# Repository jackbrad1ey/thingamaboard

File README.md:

# Thingamaboard

A custom keyboard designed and manufactured for myself. Programmed using STM32CubeIDE and Jetbrains Fleet, designed using [Ergogen](https://github.com/ergogen/ergogen), AutoCAD and Solidworks. This board was developed with portability and ergonomics in mind. It adopts a columnar, alice-like layout with three-key thumb clusters, allowing for ergonomic typing in a relatively small and portable form factor.

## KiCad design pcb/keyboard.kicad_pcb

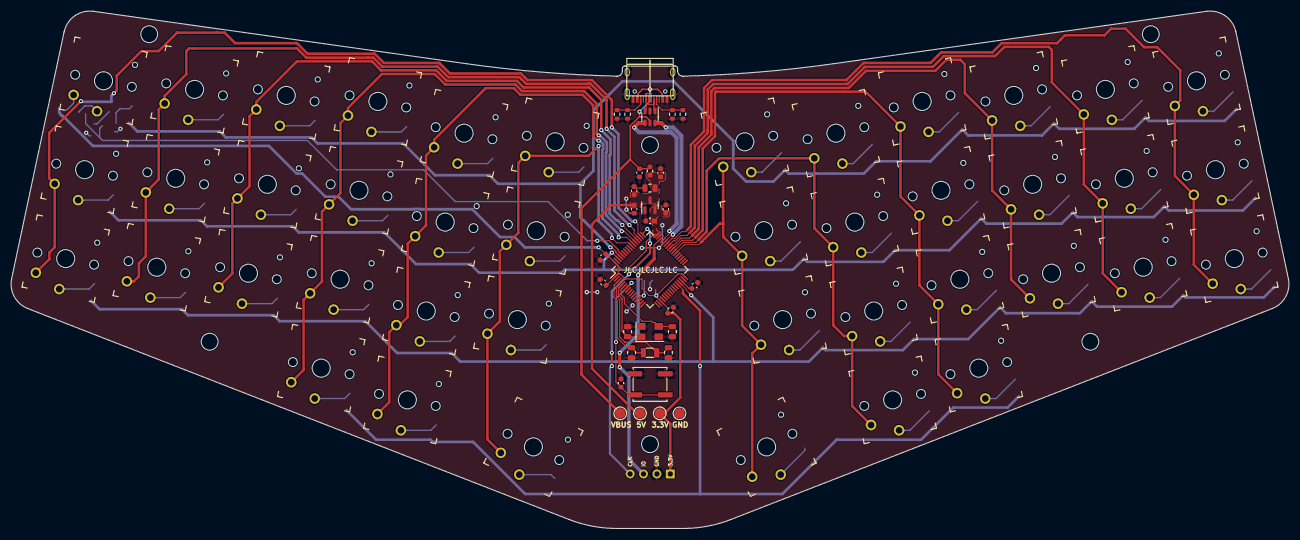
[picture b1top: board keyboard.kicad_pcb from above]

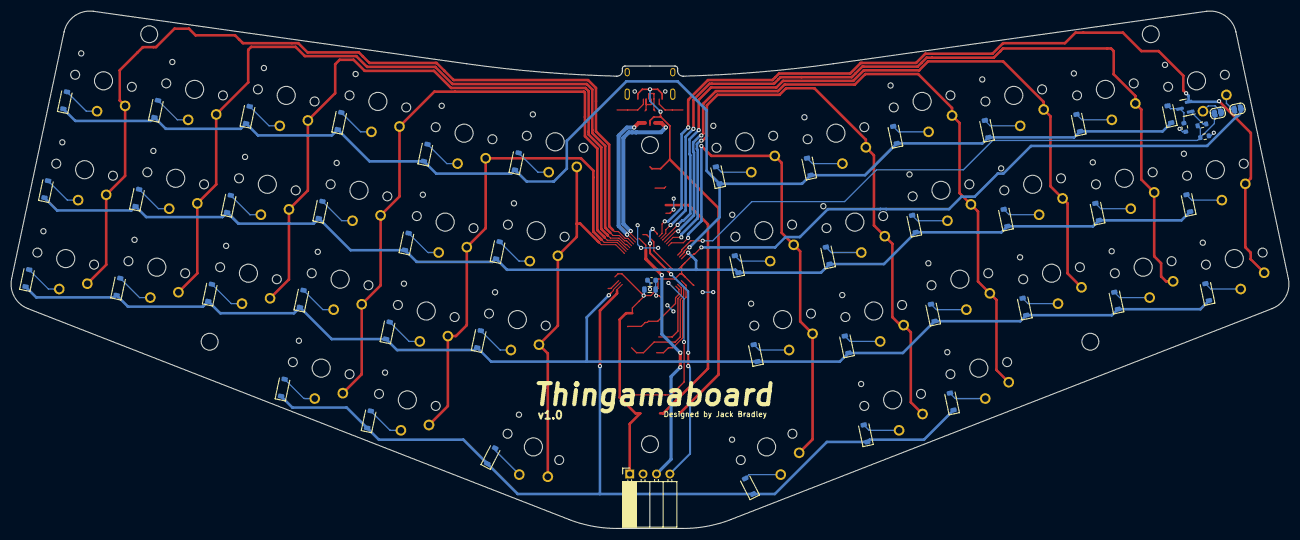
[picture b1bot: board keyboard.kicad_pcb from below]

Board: 2 copper layers, 242.5 x 98.2 mm, 131 parts (51 on the bottom side), 81 nets.

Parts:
C1, C10: 10n; C_0603_1608Metric
C2: 100n; C_0603_1608Metric
C3: 10u; C_0805_2012Metric
C4, C13, C16: 1u; C_0603_1608Metric
C5, C11, C12, C15: 100nF; C_0603_1608Metric
C6, C8: 33p; C_0805_2012Metric
C7, C9: 15p; C_0805_2012Metric
C14: 4.7u; C_0603_1608Metric
C17: 0.1u; C_0603_1608Metric
D1, D2, D3, D4, D5, D6, D7, D8, D9, D10, D11, D12, D13, D14, D15, D16, D17, D18, D19, D20, D21, D22, D23, D24, D25, D26, D27, D28, D29, D30, D31, D32, D33, D34, D35, D36, D37, D38, D39, D40, D41, D42: D_Small; D_SOD-123
FB1: FerriteBead_Small; L_0603_1608Metric
H1, H2, H3, H4, H5, H6: MountingHole; MountingHole_3.2mm_M3
J1: USB_C_Receptacle_USB2.0; TYPE-C-31-M-12
J2: Conn_01x04; PinSocket_1x04_P2.54mm_Horizontal
JP1, JP2: bridge; SolderJumper-2_P1.3mm_Open_RoundedPad1.0x1.5mm
L1: 10u; L_0805_2012Metric
Q2: BC858; SOT-23
R1, R2, R3, R4, R5, R8: 10.2k; R_0603_1608Metric
R7: 1.91k; R_0603_1608Metric
SW1, SW2, SW3, SW4, SW5, SW6, SW7, SW8, SW9, SW10, SW11, SW12, SW13, SW14, SW15, SW16, SW17, SW18, SW19, SW20, SW21, SW22, SW23, SW24, SW25, SW26, SW27, SW28, SW29, SW30, SW31, SW32, SW33, SW34, SW35, SW36, SW37, SW38, SW39, SW40, SW41, SW42: SW_Push; SW_PG1350
SW43: TS-1187A-B-A-B; SW_Push_1P1T_NO_CK_KSC6xxJ
TP1, TP2, TP3, TP4: TestPoint_Pad_D2.0mm
U1: LP3993-33B3F; SOT-23
U2: USBLC6-2SC6; SOT-23-6
U3: STM32F411RETx; LQFP-64_10x10mm_P0.5mm
Y1: 12MHz; Crystal_SMD_5032-4Pin_5.0x3.2mm
Y2: 32.768k; Crystal_SMD_3215-2Pin_3.2x1.5mm

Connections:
+3V3: C10.1, C11.1, C12.1, C13.1, C16.1, J2.1, JP1.2 (B), L1.1, TP4.1, U1.2 (VOUT), U3.1 (VBAT), U3.19 (VDD), U3.32 (VDD), U3.48 (VDD), U3.64 (VDD)
+5V: C2.1, C3.1, C4.1, C5.1, FB1.2, TP2.1, U1.3 (VIN)
/connectors/CC1: J1.A5 (CC1), R1.1, R2.1
/connectors/CC2: J1.B5 (CC2), R3.1, R4.1
/connectors/SWCLK: J2.4, U3.49 (PA14)
/connectors/SWDIO: J2.3, U3.46 (PA13)
/connectors/USB_D+: U2.4 (I/O2), U3.45 (PA12)
/connectors/USB_D-: U2.6 (I/O1), U3.44 (PA11)
/inputs/BOOT0: JP2.1 (A), R5.1, R7.1, U3.60 (BOOT0)
/inputs/NRST: C17.1, SW43.2, U3.7 (NRST)
/inputs/S1_OUT: D1.2 (A), Q2.3 (C), R8.1
/inputs/col0: Q2.2 (E), SW2.2, SW3.2, U3.50 (PA15)
/inputs/col1: SW4.2, SW5.2, SW6.2, U3.51 (PC10)
/inputs/col2: SW7.2, SW8.2, SW9.2, U3.52 (PC11)
/inputs/col3: SW10.2, SW11.2, SW12.2, SW13.2, U3.53 (PC12)
/inputs/col4: SW14.2, SW15.2, SW16.2, SW17.2, U3.54 (PD2)
/inputs/col5: SW18.2, SW19.2, SW20.2, SW21.2, U3.55 (PB3)
/inputs/col6: SW22.2, SW23.2, SW24.2, SW25.2, U3.38 (PC7)
/inputs/col7: SW26.2, SW27.2, SW28.2, SW29.2, U3.39 (PC8)
/inputs/col8: SW30.2, SW31.2, SW32.2, SW33.2, U3.40 (PC9)
/inputs/col9: SW34.2, SW35.2, SW36.2, U3.41 (PA8)
/inputs/col10: SW37.2, SW38.2, SW39.2, U3.42 (PA9)
/inputs/col11: SW40.2, SW41.2, SW42.2, U3.43 (PA10)
/inputs/row0: D1.1 (K), D4.1 (K), D7.1 (K), D10.1 (K), D14.1 (K), D18.1 (K), D22.1 (K), D26.1 (K), D30.1 (K), D34.1 (K), D37.1 (K), D40.1 (K), U3.61 (PB8)
/inputs/row1: D2.1 (K), D5.1 (K), D8.1 (K), D11.1 (K), D15.1 (K), D19.1 (K), D23.1 (K), D27.1 (K), D31.1 (K), D35.1 (K), D38.1 (K), D41.1 (K), U3.62 (PB9)
/inputs/row2: D3.1 (K), D6.1 (K), D9.1 (K), D12.1 (K), D16.1 (K), D20.1 (K), D24.1 (K), D28.1 (K), D32.1 (K), D36.1 (K), D39.1 (K), D42.1 (K), U3.29 (PB10)
/inputs/row3: D13.1 (K), D17.1 (K), D21.1 (K), D25.1 (K), D29.1 (K), D33.1 (K), U3.28 (PB2)
/stm32/HSEO_IN: C6.1, U3.5 (PH0), Y1.1
/stm32/HSEO_OUT: C8.1, U3.6 (PH1), Y1.3
/stm32/LSEO_IN: C7.1, U3.3 (PC14), Y2.1
/stm32/LSEO_OUT: C9.1, U3.4 (PC15), Y2.2
GND: C1.2, C2.2, C3.2, C4.2, C5.2, C6.2, C7.2, C8.2, C9.2, C10.2, C11.2, C12.2, C13.2, C14.2, C15.2, C16.2, C17.2, J1.A1 (GND), J1.A12 (GND), J1.B1 (GND), J1.B12 (GND), J1.S1 (SHIELD), J2.2, R1.2, R2.2, R3.2, R4.2, R5.2, R8.2, SW43.1, TP3.1, U1.1 (GND), U2.2 (GND), U3.12 (VSSA), U3.18 (VSS), U3.31 (VSS), U3.47 (VSS), U3.63 (VSS), Y1.2, Y1.4
unnamed: D2.2 (A), SW2.1
unnamed: D3.2 (A), SW3.1
unnamed: D4.2 (A), SW4.1
unnamed: D5.2 (A), SW5.1
unnamed: D6.2 (A), SW6.1
unnamed: D7.2 (A), SW7.1
unnamed: D8.2 (A), SW8.1
unnamed: D9.2 (A), SW9.1
unnamed: D10.2 (A), SW10.1
unnamed: D11.2 (A), SW11.1
unnamed: D12.2 (A), SW12.1
unnamed: D13.2 (A), SW13.1
unnamed: D14.2 (A), SW14.1
unnamed: D15.2 (A), SW15.1
unnamed: D16.2 (A), SW16.1
unnamed: D17.2 (A), SW17.1
unnamed: D18.2 (A), SW18.1
unnamed: D19.2 (A), SW19.1
unnamed: D20.2 (A), SW20.1
unnamed: D21.2 (A), SW21.1
unnamed: D22.2 (A), SW22.1
unnamed: D23.2 (A), SW23.1
unnamed: D24.2 (A), SW24.1
unnamed: D25.2 (A), SW25.1
unnamed: D26.2 (A), SW26.1
unnamed: D27.2 (A), SW27.1
unnamed: D28.2 (A), SW28.1
unnamed: D29.2 (A), SW29.1
unnamed: D30.2 (A), SW30.1
unnamed: D31.2 (A), SW31.1
unnamed: D32.2 (A), SW32.1
unnamed: D33.2 (A), SW33.1
unnamed: D34.2 (A), SW34.1
unnamed: D35.2 (A), SW35.1
unnamed: D36.2 (A), SW36.1
unnamed: D37.2 (A), SW37.1
unnamed: D38.2 (A), SW38.1
unnamed: D39.2 (A), SW39.1
unnamed: D40.2 (A), SW40.1
unnamed: D41.2 (A), SW41.1
unnamed: D42.2 (A), SW42.1
unnamed: J1.A6 (D+), J1.B6 (D+), U2.3 (I/O2)
unnamed: J1.A7 (D-), J1.B7 (D-), U2.1 (I/O1)
unnamed: JP1.1 (A), SW1.2
unnamed: JP2.2 (B), SW1.1
unnamed: Q2.1 (B), R7.2
unnamed: C14.1, U3.30 (VCAP1)
unnamed: C15.1, L1.2, U3.13 (VDDA)
VBUS: C1.1, FB1.1, J1.A4 (VBUS), J1.A9 (VBUS), J1.B4 (VBUS), J1.B9 (VBUS), TP1.1, U2.5 (VBUS)

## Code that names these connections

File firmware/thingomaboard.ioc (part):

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Mcu.Name=STM32F411R(C-E)Tx
Mcu.Package=LQFP64
Mcu.UserName=STM32F411RETx
PA10.Signal=GPIO_Output
PA11.Mode=Device_Only
PA11.Signal=USB_OTG_FS_DM
PA12.Mode=Device_Only
PA12.Signal=USB_OTG_FS_DP
PA13.Mode=Serial_Wire
PA13.Signal=SYS_JTMS-SWDIO
PA14.Mode=Serial_Wire
PA14.Signal=SYS_JTCK-SWCLK
PA15.Signal=GPIO_Output
PA8.Signal=GPIO_Output
PA9.Signal=GPIO_Output
PB10.GPIOParameters=GPIO_PuPd
PB10.GPIO_PuPd=GPIO_PULLDOWN
PB10.Signal=GPIO_Input
PB2.GPIOParameters=GPIO_PuPd
PB2.GPIO_PuPd=GPIO_PULLDOWN
PB2.Signal=GPIO_Input
PB3.Signal=GPIO_Output
PB8.GPIOParameters=GPIO_PuPd
PB8.GPIO_PuPd=GPIO_PULLDOWN
PB8.Signal=GPIO_Input
PB9.GPIOParameters=GPIO_PuPd
PB9.GPIO_PuPd=GPIO_PULLDOWN
PB9.Signal=GPIO_Input
PC10.Signal=GPIO_Output
PC11.Signal=GPIO_Output
PC12.Signal=GPIO_Output
PC14-OSC32_IN.Mode=LSE-External-Oscillator
PC14-OSC32_IN.Signal=RCC_OSC32_IN
PC15-OSC32_OUT.Mode=LSE-External-Oscillator
PC15-OSC32_OUT.Signal=RCC_OSC32_OUT
PC7.Signal=GPIO_Output
PC8.Signal=GPIO_Output
PC9.Signal=GPIO_Output
PD2.Signal=GPIO_Output
PH0\ -\ OSC_IN.Mode=HSE-External-Oscillator
PH0\ -\ OSC_IN.Signal=RCC_OSC_IN
PH1\ -\ OSC_OUT.Mode=HSE-External-Oscillator
PH1\ -\ OSC_OUT.Signal=RCC_OSC_OUT
RCC.HSE_VALUE=12000000
RCC.SYSCLKFreq_VALUE=96000000
RCC.SYSCLKSource=RCC_SYSCLKSOURCE_PLLCLK
board=custom

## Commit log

2023-06-19 initial work on layout
2023-06-19 Started initial work on PCB, added mounting holes to layout
2023-06-20 Modified layout further
2023-06-21 Working on schematic and PCB
2023-06-22 Finished off schematic
2023-06-22 Fixed up footprints, added readme
2023-06-23 Started routing
2023-06-23 Continued routing
2023-06-24 Finished routing, ready for checks
2023-06-24 Creating production files
2023-06-24 Added name to silkscreen, updated prod files
2023-06-24 Generated BOM
2023-06-25 Done, sent off for manufacturing
2023-06-26 Started working on the cad
2023-06-27 Started work on plate
2023-06-27 Create LICENSE
2023-06-27 Updated gitignore
2023-06-27 Continued work on plate
2023-06-28 Working on plate
2023-06-28 Continued plate design
2023-06-29 Designed basic top plate outline
2023-06-29 Updated readme, setup base code
2023-06-29 Updated readme, added image files
2023-06-29 Update README.md to add images
2023-06-29 Did a basic test fit in cad with the top case piece
2023-07-01 Updated outline a lil
2023-07-02 Worked on top plate
2023-07-03 Began work on the code
2023-07-04 Setup accurate us timer
2023-07-04 cadded 1U keycaps
2023-07-04 Extended top case width
2023-07-05 Slight change
2023-07-06 Worked on top case
2023-07-07 Continued work on case
2023-07-09 Modified HID middleware to keyboard HID device
2023-07-10 Continued work on firmware
2023-07-10 Fixed some small bugs
2023-07-10 Added HID keycodes
2023-07-12 Created base keymap
2023-07-12 working on key scanning
2023-07-12 key scanning added
2023-07-14 Updated key scanning
2023-07-17 Added interactive BOM for assembly
2023-07-22 Continued firmware development
2023-07-23 ready for testing
2023-07-23 Added some basic testing code
2023-07-27 Produced working firmware, identified hardware flaw
2023-07-30 Implemented dedicated boot0 key
2023-07-30 Working on CAD
2023-07-30 Reworking debounce system
2023-07-30 Fixed up firmware keypresses
2023-10-25 Case design done
2023-10-28 Continued case CAD, made renders
2023-10-28 Added case render
